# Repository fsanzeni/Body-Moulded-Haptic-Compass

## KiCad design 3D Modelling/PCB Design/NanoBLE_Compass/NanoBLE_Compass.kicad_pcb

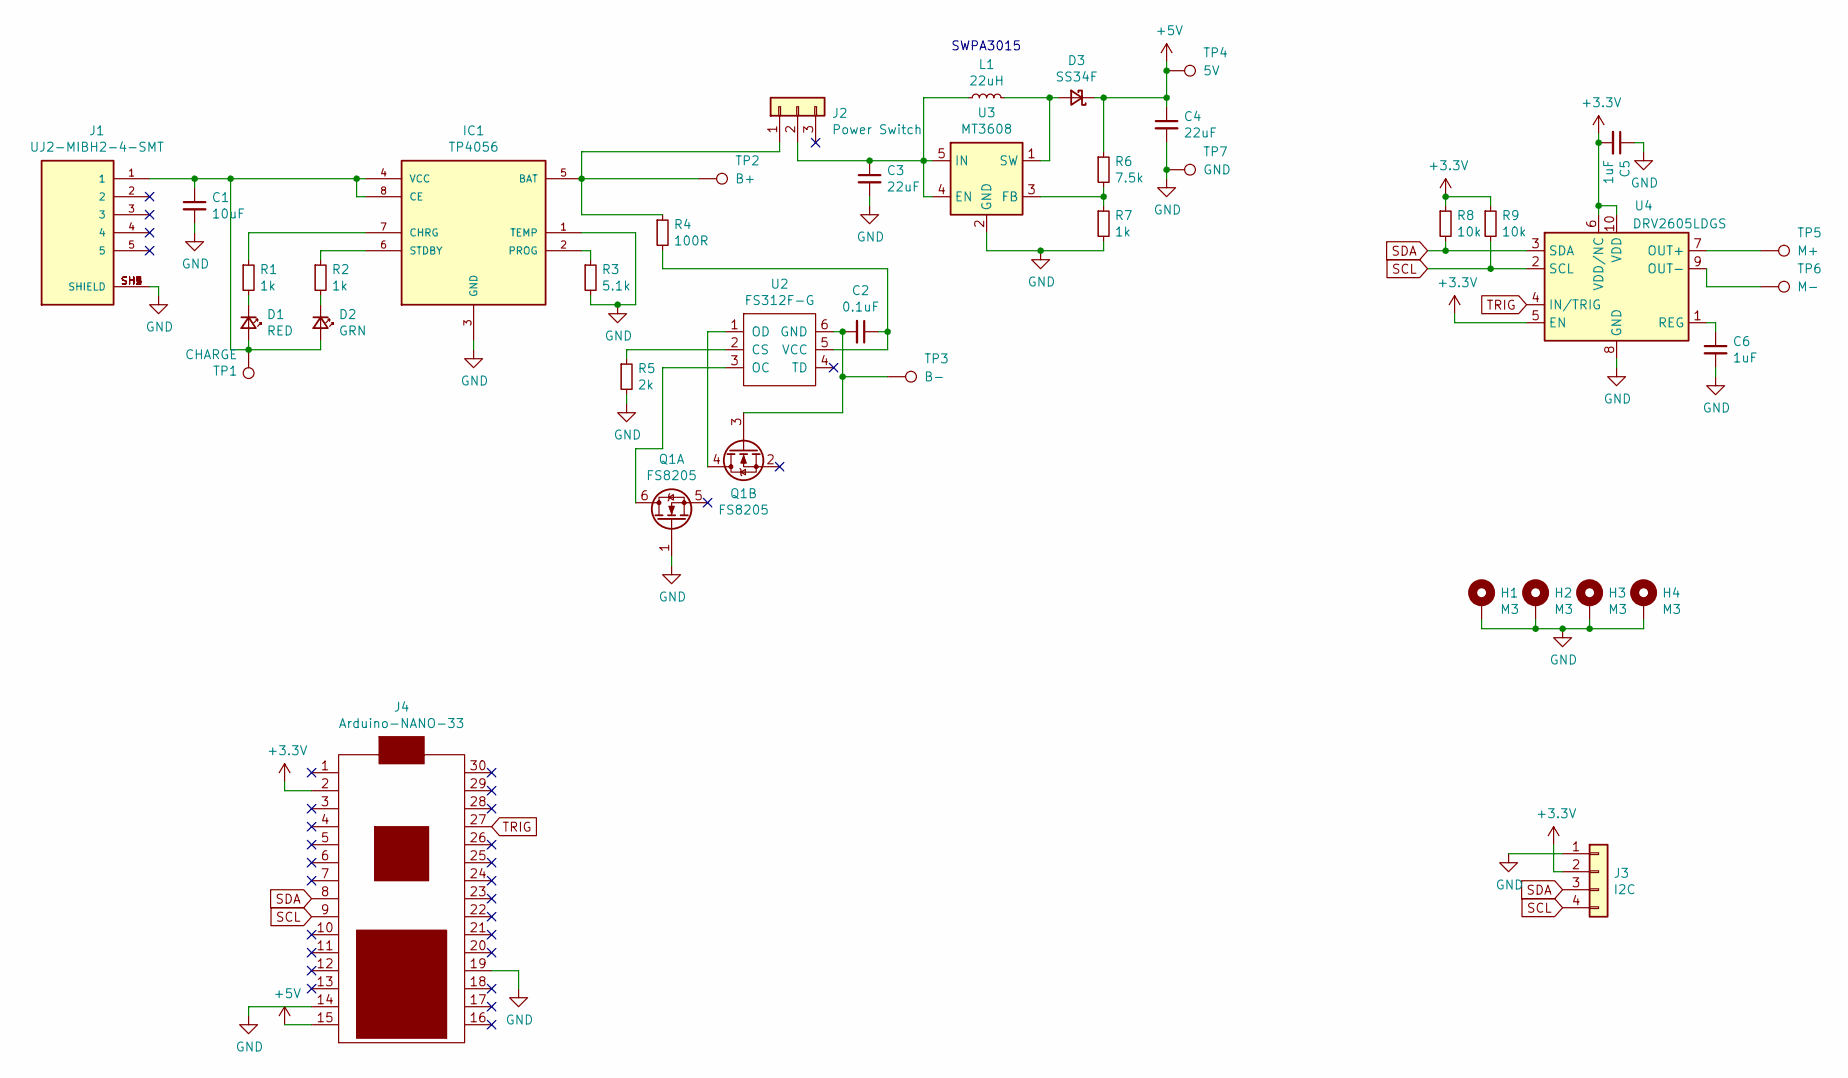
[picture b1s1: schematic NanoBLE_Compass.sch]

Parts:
C1: 10uF; C_0603_1608Metric
C2: 0.1uF; C_0603_1608Metric
C3, C4: 22uF; C_0805_2012Metric
C5, C6: 1uF; C_0603_1608Metric
D1: RED; LED_0603_1608Metric
D2: GRN; LED_0603_1608Metric
D3: SS34F; D_SMA
H1, H2, H3, H4: M3; MountingHole_3.2mm_M3_Pad
IC1: TP4056; SOP-8
J1: UJ2-MIBH2-4-SMT; CUI_UJ2-MIBH2-4-SMT; PART_REV 1.0
J2: Power Switch; PinSocket_1x03_P2.54mm_Vertical
J3: I2C; PinSocket_1x04_P2.54mm_Vertical
J4: Arduino-NANO-33; nano33_Footprint_SMD_Castell
L1: 22uH; SWPA3015
Q1: FS8205; SOT-23-6
R1, R2, R7: 1k; R_0603_1608Metric
R3: 5.1k; R_0603_1608Metric
R4: 100R; R_0603_1608Metric
R5: 2k; R_0603_1608Metric
R6: 7.5k; R_0603_1608Metric
R8, R9: 10k; R_0603_1608Metric
TP1: CHARGE; TestPoint_Pad_D1.0mm
TP2: B+; TestPoint_THTPad_2.0x2.0mm_Drill1.0mm
TP3: B-; TestPoint_THTPad_2.0x2.0mm_Drill1.0mm
TP4: 5V; TestPoint_Pad_D1.0mm
TP5: M+; TestPoint_THTPad_2.0x2.0mm_Drill1.0mm
TP6: M-; TestPoint_THTPad_2.0x2.0mm_Drill1.0mm
TP7: GND; TestPoint_Pad_D1.0mm
U2: FS312F-G; SOT-23-6
U3: MT3608; SOT-23-6
U4: DRV2605LDGS; VSSOP-10_3x3mm_P0.5mm

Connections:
+3V3: C5.2, J3.2, J4.2, R8.1, R9.1, U4.5 (EN), U4.6 (VDD/NC), U4.10 (VDD)
+5V: C4.1, D3.1 (K), J4.15, R6.1, TP4.1
GND: C1.2, C3.2, C4.2, C5.1, C6.2, H1.1, H2.1, H3.1, H4.1, IC1.1 (TEMP), IC1.3 (GND), J1.SH1 (SHIELD), J1.SH2 (SHIELD), J1.SH3 (SHIELD), J1.SH4 (SHIELD), J1.SH5 (SHIELD), J3.1, J4.14, J4.19, Q1.1 (G), R3.2, R5.2, R7.2, TP7.1, U3.2 (GND), U4.8 (GND)
unnamed: C1.1, D1.2 (A), D2.2 (A), IC1.4 (VCC), IC1.8 (CE), J1.1, TP1.1
unnamed: C2.1, R4.2, U2.5 (VCC)
unnamed: C2.2, Q1.3 (G), TP3.1, U2.6 (GND)
unnamed: C3.1, J2.2, L1.1, U3.4 (EN), U3.5 (IN)
unnamed: C6.1, U4.1 (REG)
unnamed: D1.1 (K), R1.2
unnamed: D2.1 (K), R2.2
unnamed: D3.2 (A), L1.2, U3.1 (SW)
unnamed: IC1.2 (PROG), R3.1
unnamed: IC1.5 (BAT), J2.1, R4.1, TP2.1
unnamed: IC1.6 (STDBY), R2.1
unnamed: IC1.7 (CHRG), R1.1
unnamed: Q1.4 (D), U2.1 (OD)
unnamed: Q1.6 (D), U2.3 (OC)
unnamed: R5.1, U2.2 (CS)
unnamed: R6.2, R7.1, U3.3 (FB)
unnamed: TP5.1, U4.7 (OUT+)
unnamed: TP6.1, U4.9 (OUT-)
SCL: J3.4, J4.9, R9.2, U4.2 (SCL)
SDA: J3.3, J4.8, R8.2, U4.3 (SDA)
TRIG: J4.27, U4.4 (IN/TRIG)

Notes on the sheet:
SWPA3015

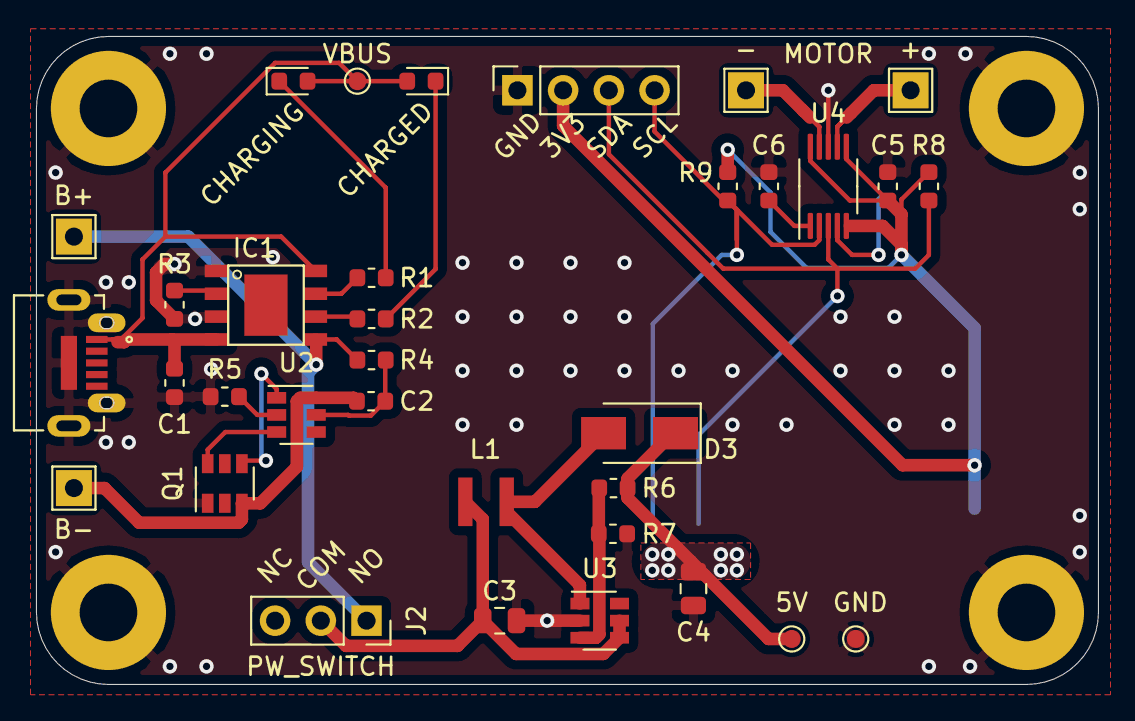
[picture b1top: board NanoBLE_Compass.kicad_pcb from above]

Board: 2 copper layers, 59.0 x 36.0 mm, 39 parts (1 on the bottom side), 24 nets.

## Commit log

2023-04-23 Initial ccommit
    readme missing - will add after submission
2023-04-23 Fixed PATH
